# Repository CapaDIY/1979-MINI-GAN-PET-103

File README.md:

# 1979-MINI-GAN-PET-103

PCB and schematics based on Youtube video by [David Hilowitz Music](https://www.youtube.com/watch?v=ADZXv5DA7Ek).

Here you will get PCB layouts based on the original boards and KiCad source files that you can download and customize to your needs.

Please share any updates and improvments!

[Visit www.capadiy.com](https://www.capadiy.com)

Instagram: [@CapaDIY](https://www.instagram.com/CapaDIY)

Patreon: [https://www.patreon.com/CapaDIY](https://www.patreon.com/CapaDIY)

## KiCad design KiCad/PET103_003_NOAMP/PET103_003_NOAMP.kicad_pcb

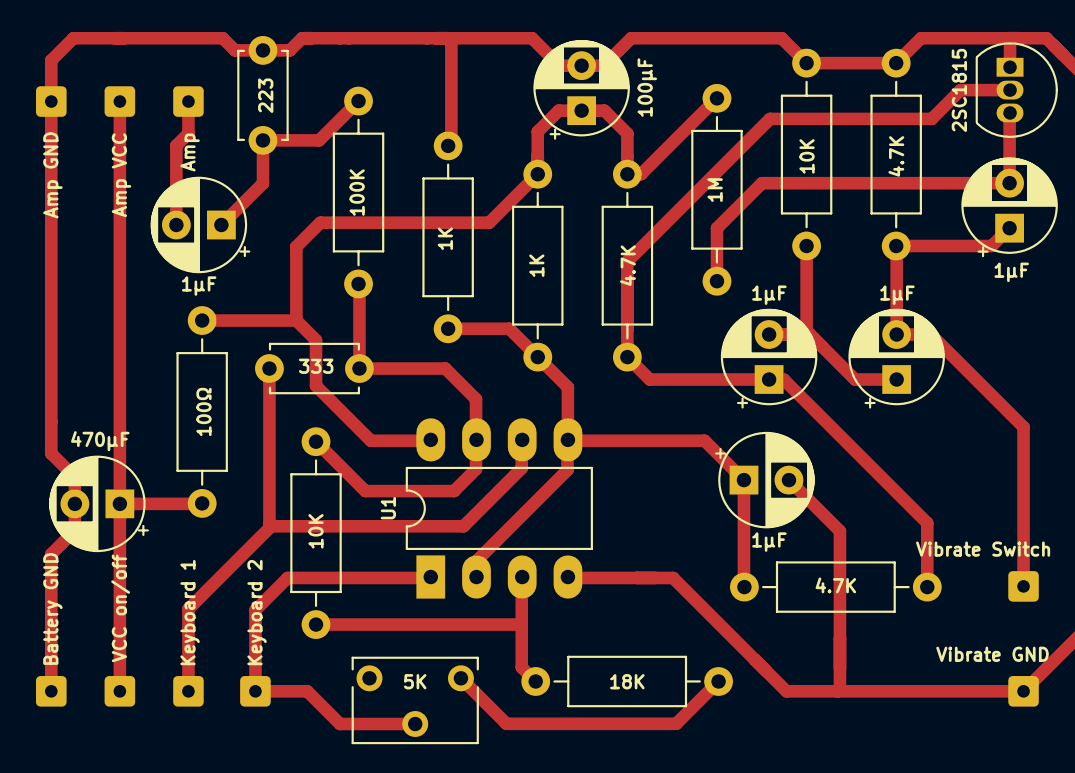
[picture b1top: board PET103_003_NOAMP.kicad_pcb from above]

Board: 2 copper layers, 32 parts (0 on the bottom side), 15 nets.

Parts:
C2: 470µF; CP_Radial_D5.0mm_P2.50mm
C10: 100µF; CP_Radial_D5.0mm_P2.50mm
C11, C13, C15, C16, C17: 1µF; CP_Radial_D5.0mm_P2.50mm
C12: 223; C_Disc_D4.7mm_W2.5mm_P5.00mm
C14: 333; C_Disc_D4.7mm_W2.5mm_P5.00mm
J1: Battery GND; SolderWire-0.15sqmm_1x01_D0.5mm_OD1.5mm
J2: Amp VCC; SolderWire-0.15sqmm_1x01_D0.5mm_OD1.5mm
J3: Amp GND; SolderWire-0.15sqmm_1x01_D0.5mm_OD1.5mm
J4: Vibrate GND; SolderWire-0.15sqmm_1x01_D0.5mm_OD1.5mm
J5: VCC on/off; SolderWire-0.15sqmm_1x01_D0.5mm_OD1.5mm
J8: Amp; SolderWire-0.15sqmm_1x01_D0.5mm_OD1.5mm
J9: Keyboard 1; SolderWire-0.15sqmm_1x01_D0.5mm_OD1.5mm
J10: Keyboard 2; SolderWire-0.15sqmm_1x01_D0.5mm_OD1.5mm
J11: Vibrate Switch; SolderWire-0.15sqmm_1x01_D0.5mm_OD1.5mm
Q1: 2SC1815; TO-92_Inline
R2: 100Ω; R_Axial_DIN0207_L6.3mm_D2.5mm_P10.16mm_Horizontal
R3, R7, R10: 4.7K; R_Axial_DIN0207_L6.3mm_D2.5mm_P10.16mm_Horizontal
R4: 1M; R_Axial_DIN0207_L6.3mm_D2.5mm_P10.16mm_Horizontal
R5: 100K; R_Axial_DIN0207_L6.3mm_D2.5mm_P10.16mm_Horizontal
R6, R8: 1K; R_Axial_DIN0207_L6.3mm_D2.5mm_P10.16mm_Horizontal
R9, R11: 10K; R_Axial_DIN0207_L6.3mm_D2.5mm_P10.16mm_Horizontal
R12: 18K; R_Axial_DIN0207_L6.3mm_D2.5mm_P10.16mm_Horizontal
R13: 5K; Potentiometer_Bourns_3266W_Vertical
U1: LA6458; DIP-8_W7.62mm_LongPads

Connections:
G: C11.2, J8.1
GND: C2.2, C10.2, C12.2, C16.2, J1.1, J3.1, J4.1, Q1.1, R7.2, R8.1, R9.2, U1.4
unnamed: C10.1, R2.1, R3.2, R4.2, R6.2, U1.8
unnamed: C11.1, C12.1, R5.1
unnamed: C13.2, Q1.3, R4.1
unnamed: C14.1, R5.2, R11.2, U1.7
unnamed: C15.1, C17.2, R9.1
unnamed: C16.1, R6.1, R8.2, R10.2, U1.2, U1.5
unnamed: C17.1, Q1.2, R3.1, R10.1
unnamed: R11.1, R12.2, U1.3
unnamed: R12.1, R13.1
P: J10.1, R13.2, U1.1
V: C13.1, C15.2, J11.1, R7.1
VCC: C2.1, J2.1, J5.1, R2.2
Y: C14.2, J9.1, U1.6

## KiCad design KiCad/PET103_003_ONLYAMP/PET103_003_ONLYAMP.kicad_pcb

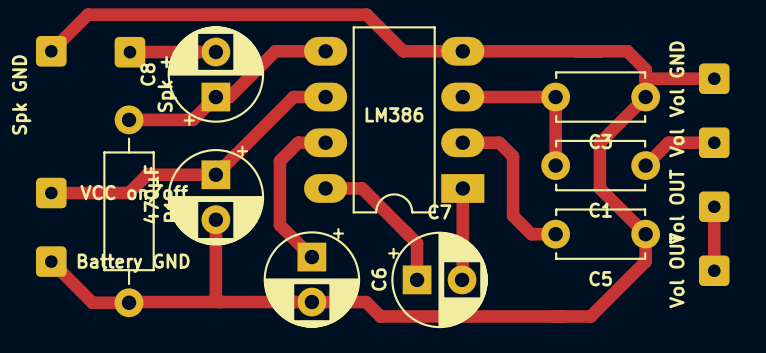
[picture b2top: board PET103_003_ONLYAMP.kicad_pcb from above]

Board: 2 copper layers, 17 parts (0 on the bottom side), 11 nets.

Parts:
C1, C5: 0.27µF; C_Disc_D4.7mm_W2.5mm_P5.00mm
C2, C8: 470µF; CP_Radial_D5.0mm_P2.50mm
C3: 47pF; C_Disc_D4.7mm_W2.5mm_P5.00mm
C6, C7: 10µF; CP_Radial_D5.0mm_P2.50mm
J1: Battery GND; SolderWire-0.15sqmm_1x01_D0.5mm_OD1.5mm
J2: Spk GND; SolderWire-0.15sqmm_1x01_D0.5mm_OD1.5mm
J3: Vol GND; SolderWire-0.15sqmm_1x01_D0.5mm_OD1.5mm
J4, J8: Vol OUT; SolderWire-0.15sqmm_1x01_D0.5mm_OD1.5mm
J5: VCC on/off; SolderWire-0.15sqmm_1x01_D0.5mm_OD1.5mm
J6: Spk +; SolderWire-0.15sqmm_1x01_D0.5mm_OD1.5mm
J7: Vol; SolderWire-0.15sqmm_1x01_D0.5mm_OD1.5mm
R1: 100Ω; R_Axial_DIN0207_L6.3mm_D2.5mm_P10.16mm_Horizontal
U2: LM386; DIP-8_W7.62mm_LongPads

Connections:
GND: C2.2, C3.1, C5.1, C6.2, J1.1, J2.1, J3.1, R1.2, U2.4
unnamed: C1.2, C3.2, U2.3
unnamed: C5.2, U2.2
unnamed: C6.1, U2.7
unnamed: C7.1, U2.8
unnamed: C7.2, U2.1
unnamed: C8.1, R1.1, U2.5
unnamed: J4.1, J8.1
O: C1.1, J7.1
VCC: C2.1, J5.1, U2.6
W: C8.2, J6.1

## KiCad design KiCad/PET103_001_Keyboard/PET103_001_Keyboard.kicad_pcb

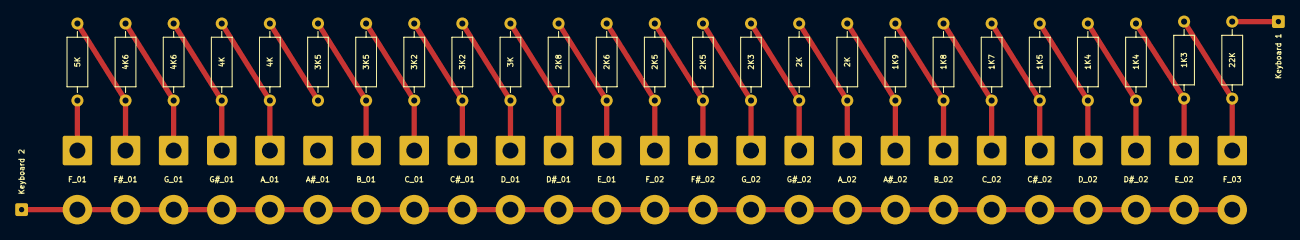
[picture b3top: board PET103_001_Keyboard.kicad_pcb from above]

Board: 2 copper layers, 52 parts (0 on the bottom side), 27 nets.

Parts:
J1: Keyboard 1; SolderWire-0.15sqmm_1x01_D0.5mm_OD1.5mm
J2: Keyboard 2; SolderWire-0.15sqmm_1x01_D0.5mm_OD1.5mm
R1: 5K; R_Axial_DIN0207_L6.3mm_D2.5mm_P10.16mm_Horizontal
R2, R3: 4K6; R_Axial_DIN0207_L6.3mm_D2.5mm_P10.16mm_Horizontal
R4, R5: 4K; R_Axial_DIN0207_L6.3mm_D2.5mm_P10.16mm_Horizontal
R6, R7: 3K5; R_Axial_DIN0207_L6.3mm_D2.5mm_P10.16mm_Horizontal
R8, R9: 3K2; R_Axial_DIN0207_L6.3mm_D2.5mm_P10.16mm_Horizontal
R10: 3K; R_Axial_DIN0207_L6.3mm_D2.5mm_P10.16mm_Horizontal
R11: 2K8; R_Axial_DIN0207_L6.3mm_D2.5mm_P10.16mm_Horizontal
R12: 2K6; R_Axial_DIN0207_L6.3mm_D2.5mm_P10.16mm_Horizontal
R13, R14: 2K5; R_Axial_DIN0207_L6.3mm_D2.5mm_P10.16mm_Horizontal
R15: 2K3; R_Axial_DIN0207_L6.3mm_D2.5mm_P10.16mm_Horizontal
R16, R17: 2K; R_Axial_DIN0207_L6.3mm_D2.5mm_P10.16mm_Horizontal
R18: 1K9; R_Axial_DIN0207_L6.3mm_D2.5mm_P10.16mm_Horizontal
R19: 1K8; R_Axial_DIN0207_L6.3mm_D2.5mm_P10.16mm_Horizontal
R20: 1K7; R_Axial_DIN0207_L6.3mm_D2.5mm_P10.16mm_Horizontal
R21: 1K5; R_Axial_DIN0207_L6.3mm_D2.5mm_P10.16mm_Horizontal
R22, R23: 1K4; R_Axial_DIN0207_L6.3mm_D2.5mm_P10.16mm_Horizontal
R24: 1K3; R_Axial_DIN0207_L6.3mm_D2.5mm_P10.16mm_Horizontal
R25: 22K; R_Axial_DIN0207_L6.3mm_D2.5mm_P10.16mm_Horizontal
SW1: F_01; SolderWire-1.5sqmm_1x02_P7.8mm_D1.7mm_OD3.9mm
SW2: F#_01; SolderWire-1.5sqmm_1x02_P7.8mm_D1.7mm_OD3.9mm
SW3: G_01; SolderWire-1.5sqmm_1x02_P7.8mm_D1.7mm_OD3.9mm
SW4: G#_01; SolderWire-1.5sqmm_1x02_P7.8mm_D1.7mm_OD3.9mm
SW5: A_01; SolderWire-1.5sqmm_1x02_P7.8mm_D1.7mm_OD3.9mm
SW6: A#_01; SolderWire-1.5sqmm_1x02_P7.8mm_D1.7mm_OD3.9mm
SW7: B_01; SolderWire-1.5sqmm_1x02_P7.8mm_D1.7mm_OD3.9mm
SW8: C_01; SolderWire-1.5sqmm_1x02_P7.8mm_D1.7mm_OD3.9mm
SW9: C#_01; SolderWire-1.5sqmm_1x02_P7.8mm_D1.7mm_OD3.9mm
SW10: D_01; SolderWire-1.5sqmm_1x02_P7.8mm_D1.7mm_OD3.9mm
SW11: D#_01; SolderWire-1.5sqmm_1x02_P7.8mm_D1.7mm_OD3.9mm
SW12: E_01; SolderWire-1.5sqmm_1x02_P7.8mm_D1.7mm_OD3.9mm
SW13: F_02; SolderWire-1.5sqmm_1x02_P7.8mm_D1.7mm_OD3.9mm
SW14: F#_02; SolderWire-1.5sqmm_1x02_P7.8mm_D1.7mm_OD3.9mm
SW15: G_02; SolderWire-1.5sqmm_1x02_P7.8mm_D1.7mm_OD3.9mm
SW16: G#_02; SolderWire-1.5sqmm_1x02_P7.8mm_D1.7mm_OD3.9mm
SW17: A_02; SolderWire-1.5sqmm_1x02_P7.8mm_D1.7mm_OD3.9mm
SW18: A#_02; SolderWire-1.5sqmm_1x02_P7.8mm_D1.7mm_OD3.9mm
SW19: B_02; SolderWire-1.5sqmm_1x02_P7.8mm_D1.7mm_OD3.9mm
SW20: C_02; SolderWire-1.5sqmm_1x02_P7.8mm_D1.7mm_OD3.9mm
SW21: C#_02; SolderWire-1.5sqmm_1x02_P7.8mm_D1.7mm_OD3.9mm
SW22: D_02; SolderWire-1.5sqmm_1x02_P7.8mm_D1.7mm_OD3.9mm
SW23: D#_02; SolderWire-1.5sqmm_1x02_P7.8mm_D1.7mm_OD3.9mm
SW24: E_02; SolderWire-1.5sqmm_1x02_P7.8mm_D1.7mm_OD3.9mm
SW25: F_03; SolderWire-1.5sqmm_1x02_P7.8mm_D1.7mm_OD3.9mm

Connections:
unnamed: R1.1, SW1.1
unnamed: R1.2, R2.1, SW2.1
unnamed: R2.2, R3.1, SW3.1
unnamed: R3.2, R4.1, SW4.1
unnamed: R4.2, R5.1, SW5.1
unnamed: R5.2, R6.1, SW6.1
unnamed: R6.2, R7.1, SW7.1
unnamed: R7.2, R8.1, SW8.1
unnamed: R8.2, R9.1, SW9.1
unnamed: R9.2, R10.1, SW10.1
unnamed: R10.2, R11.1, SW11.1
unnamed: R11.2, R12.1, SW12.1
unnamed: R12.2, R13.1, SW13.1
unnamed: R13.2, R14.1, SW14.1
unnamed: R14.2, R15.1, SW15.1
unnamed: R15.2, R16.1, SW16.1
unnamed: R16.2, R17.1, SW17.1
unnamed: R17.2, R18.1, SW18.1
unnamed: R18.2, R19.1, SW19.1
unnamed: R19.2, R20.1, SW20.1
unnamed: R20.2, R21.1, SW21.1
unnamed: R21.2, R22.1, SW22.1
unnamed: R22.2, R23.1, SW23.1
unnamed: R23.2, R24.1, SW24.1
unnamed: R24.2, R25.1, SW25.1
P: J2.1, SW1.2, SW2.2, SW3.2, SW4.2, SW5.2, SW6.2, SW7.2, SW8.2, SW9.2, SW10.2, SW11.2, SW12.2, SW13.2, SW14.2, SW15.2, SW16.2, SW17.2, SW18.2, SW19.2, SW20.2, SW21.2, SW22.2, SW23.2, SW24.2, SW25.2
Y: J1.1, R25.2

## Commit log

2022-10-22 Updated schematics and PCB with new symbols and rearranged the layout. Added one more datasheet and KiCad symbol for LA4140.
2022-10-22 Schematics PDF
2022-10-23 Print for keyboard PCB
2022-10-23 KiCad and schematics for keyboard
2022-10-23 EPS vector files of keyboard PCB layout
2022-10-23 Updated schematics
2022-10-23 Updated BOM
2022-10-25 Untested. LM386 version instead of LA4140
2022-10-29 More KiCad tinkering...
